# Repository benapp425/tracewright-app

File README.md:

<h1 align="center">Tracewright</h1>

<p align="center"><b>KiCad boards, designed with Claude.</b><br>
Describe a board or open one you have. Claude designs, places, routes and checks it with you,<br>
live in KiCad, then sends it to the fab.</p>

## Features

**Design with Claude**
- **A chat beside the board.** Claude reads the schematic and board, runs the checks and makes changes with its own design tools.
- **Start from a floorplan.** Drag the board's outline, mounting holes, connectors and main parts into place. Claude lays the board out from it.
- **Live in KiCad.** Placement and routing appear in KiCad's PCB Editor as Claude works.
- **You stay in control.** Claude keeps a visible plan, asks questions as cards and reads the notes you send while it works. Each turn shows what it changed and can be undone.
- **Edit it yourself.** Move, turn and lock parts, route tracks and pairs, tune lengths, draw pours and keep-outs on the board; change a part's value or footprint and rename nets on the schematic. ⌘Z undoes each step.
- **Flags as threads.** Flag a spot on the board or schematic with a request or a question, and draw on it: where a track should go, what to keep clear. Claude answers in the thread.
- **Needs your OK.** Nothing interrupts a run. Afterwards, a short list shows what Claude went ahead with that you may want to see (a swapped part, a moved connector, your own work changed), to keep or undo.
- **Notes that read like a person wrote them.** One short line on the sheet beside the part it explains; the reasoning and its sources in the design notes, shown when you hover the part.
- **Placement with reasons.** Pick a part to see why it is where it is. Keep parts near a pin, together, apart or at an edge; Claude places around it, in stages, and scores the result.
- **A routing plan.** Each net is routed by the router, routed first with its rules (pairs, clocks, switch nodes, heavy currents), or left for you (RF, current sense, high voltage), with its reason. Pick the router's preset and keep a net to chosen layers.
- **Up to 12 layers, and HDI.** Claude plans the stack-up and routes every signal layer. HDI (vias in pads, microvias, blind vias) stays off unless you turn it on.
- **Dense boards.** Before routing, each BGA is broken out: a via on every ball that needs one, each signal's escape out to the edge of the ball field layer by layer, and the parts under it moved off its via spots. Fine-pitch connectors get a via beside each pad, alternating sides. On a breakout board, the free GPIO move to the connector pins that lie the way they leave the chip. The router then negotiates: nets may cross at a rising price until none share copper, and it names the spots that stayed contested. The board says first whether it can be routed in its room and layers.
- **Pairs to their budget.** Click a pair to see its skew against what its interface allows; the route tunes pairs and length groups within their budgets.
- **Both sides from the start.** The setup's floorplan puts blocks and connectors on the top or the bottom.
- **Where tracks fit.** See the crowded parts of the board, hover any point to see what keeps a track out, and give an area its own rules (keep-out, no vias, finer tracks, more spacing).
- **Cost before you run.** See a request's likely cost and share of your plan's limit before you send it.
- **My parts.** Save parts you have checked, with their footprints, 3D models and notes, for every project.
- **Talk, attach, point.** Dictate a message, drop in pictures and data sheets, or type @ to point Claude at a part, net or sheet.
- **Run monitor.** A full-screen view of a run: the plan, the stages, the board as it grows, and how much of your Claude plan's limit is used.

**Check it**
- **62 design checks.** Schematic integrity (pinouts, packages, voltage domains), BOM, placement, routing quality, fab limits, assembly, signal integrity and power (regulators, heat, voltage drop, switchers, pours). Each says what it examined, and each is tested against a planted fault.
- **Simulate the board as laid out.** The voltage drop and current density in a supply's copper, the board's heat, where a fast net's return current runs (and the loop it opens round a gap), a net's impedance and edge at the far end with the series resistor that would tame it, crosstalk, a rail's impedance against its target, and circuit blocks from the schematic in ngspice.
- **Sign-off.** Before anything is ordered: the verdict, every requirement with its evidence (checks, calculations, simulations, regulator heat), the waivers you approved, and what only the built board can show.
- **Compare versions.** See what moved and which copper changed since any checkpoint.
- **Bring-up.** A checklist for the built board, with each reading checked against the plan, and a firmware starter: the pin map and a bring-up sketch from the schematic.

**Build it**
- **Order in one place.** JLCPCB turnkey or self-assembly, with a readiness list and a price estimate. Upload to PCBWay in one click.
- **Stock watch.** Warns when a part runs short of what an order needs, and finds in-stock stand-ins.
- **Save money.** Exact JLC Basic equivalents for Extended parts.
- **Parts lists.** For DigiKey, Mouser and LCSC.
- **Make.** The BOM's health, a test-point plan, a fab drawing and assembly drawings, a V-scored panel with rails and fiducials, the enclosure fit with an OpenSCAD box to start from, and your blocks: circuits that worked once, saved to use again.

## Download

1. Download **Tracewright-&lt;version&gt;-mac.zip** from the [latest release](../../releases/latest) and move **Tracewright.app** to Applications.
2. Open it with **right-click ▸ Open** the first time (the app is not notarized yet).
3. Tracewright installs its engine in `~/.tracewright-app`, then asks you to create an account.

### Requirements

- macOS 12 or later, on Apple silicon or Intel
- Python 3.10 or later ([python.org](https://www.python.org/downloads/macos/) or Homebrew)
- KiCad 9 or 10 ([kicad.org](https://www.kicad.org/download/macos/))
- [Claude Code](https://claude.com/claude-code), signed in, or an Anthropic API key
- Optional: Java 17+ and Freerouting 2.x for whole-board autorouting

## Install from source

```sh
git clone https://github.com/benapp425/tracewright-app.git && cd tracewright-app
sh install.sh
```

This installs Tracewright in `~/.tracewright-app`, adds the `tracewright` command, and builds
`~/Applications/Tracewright.app` (the Xcode command line tools are needed: `xcode-select --install`).
Run it again to update. `sh install.sh --uninstall` removes the app and keeps your projects and settings.
`tracewright doctor` reports what it found.

## Getting started

1. **Create your account.** The first account owns the app. Google sign-in can be set up in
   Settings ▸ Account. Forgot your password? Use **Forgot?** on the sign-in screen, or run
   `tracewright account reset EMAIL`.
2. **Finish setup.** Tracewright checks KiCad and Claude, then asks for a theme and a workflow.
3. **Start a project.** Describe a new board, import a KiCad project (or Altium, Eagle, PADS,
   CADSTAR, Fabmaster or P-CAD), open the demo, or get project ideas.
4. **Sign off and order.** Review the findings and waivers in Checks ▸ Sign-off and sign the design off. Parts ▸ Order then
   prepares the files and sends them to the fab.

To see Claude's edits live in KiCad, enable KiCad's API (**Preferences ▸ Plugins ▸ Enable KiCad API**),
restart KiCad and open the board in the PCB Editor.

## Project structure

```
my-board/
  tracewright.json      project settings: fab, sourcing, checks, stages
  BRIEF.md              the original description
  CLAUDE.md             instructions for Claude
  .claude/              skills for each stage, lessons, permissions
  hardware/<name>/      the KiCad project, with design-notes.json (the reasoning behind the schematic)
                        and placement-plan.json (why each part is where it is, and what to keep)
  design/               scripts Claude writes, and project-specific checks
  docs/                 requirements, architecture, decisions, parts, review, bring-up
  tools/tw/             the toolkit (./tw <command>), usable without the app
  build/                reports, plots and fab outputs (not in git)
```

Every project works without the app: `./tw check`, `./tw route`, `./tw escape`, `./tw space` and
`./tw outputs` run from the project folder, and Claude Code picks up the same instructions and skills there.

## Privacy

Tracewright runs on your Mac and keeps your projects there. When Claude works on a project, what it
reads (files, renders, check results) goes to Anthropic through your Claude Code sign-in or API key.
Part lookups query JLCPCB, LCSC and EasyEDA for the parts you look up, and once a day the stock watch asks
about the parts on a board you open (Settings ▸ Watch part stock turns it off). Dictation uses Apple's speech recognition, on the Mac when
it can; in a browser, the browser's own speech service. Board files are uploaded only
when you order or sync a project with GitHub. Accounts are stored in the app's data folder, with
passwords kept only as salted hashes. Once a day the app checks GitHub for a newer release
(Settings ▸ About turns this off).

## Server deployment

Tracewright can also run on a server as a web app, with accounts, uploads and GitHub import.
See [DEPLOY.md](DEPLOY.md).

## Development

```sh
python3 -m venv .venv && .venv/bin/pip install -e .
TW_ACCOUNTS=0 .venv/bin/python -m tracewright serve --port 8799   # no sign-in while developing
.venv/bin/python tests/run_tests.py                              # tests (some need KiCad)
.venv/bin/python tracewright/toolkit/tw/cli.py selftest          # every check catches its planted fault
sh macos/release.sh                                              # the downloadable app, in dist/
```

See [CHANGELOG.md](CHANGELOG.md) for release notes.

## License

MIT (see [LICENSE](LICENSE)). Tracewright works with, but does not include, KiCad (GPL-3.0+) and,
optionally, Freerouting (GPL-3.0). See [THIRD_PARTY.md](THIRD_PARTY.md).

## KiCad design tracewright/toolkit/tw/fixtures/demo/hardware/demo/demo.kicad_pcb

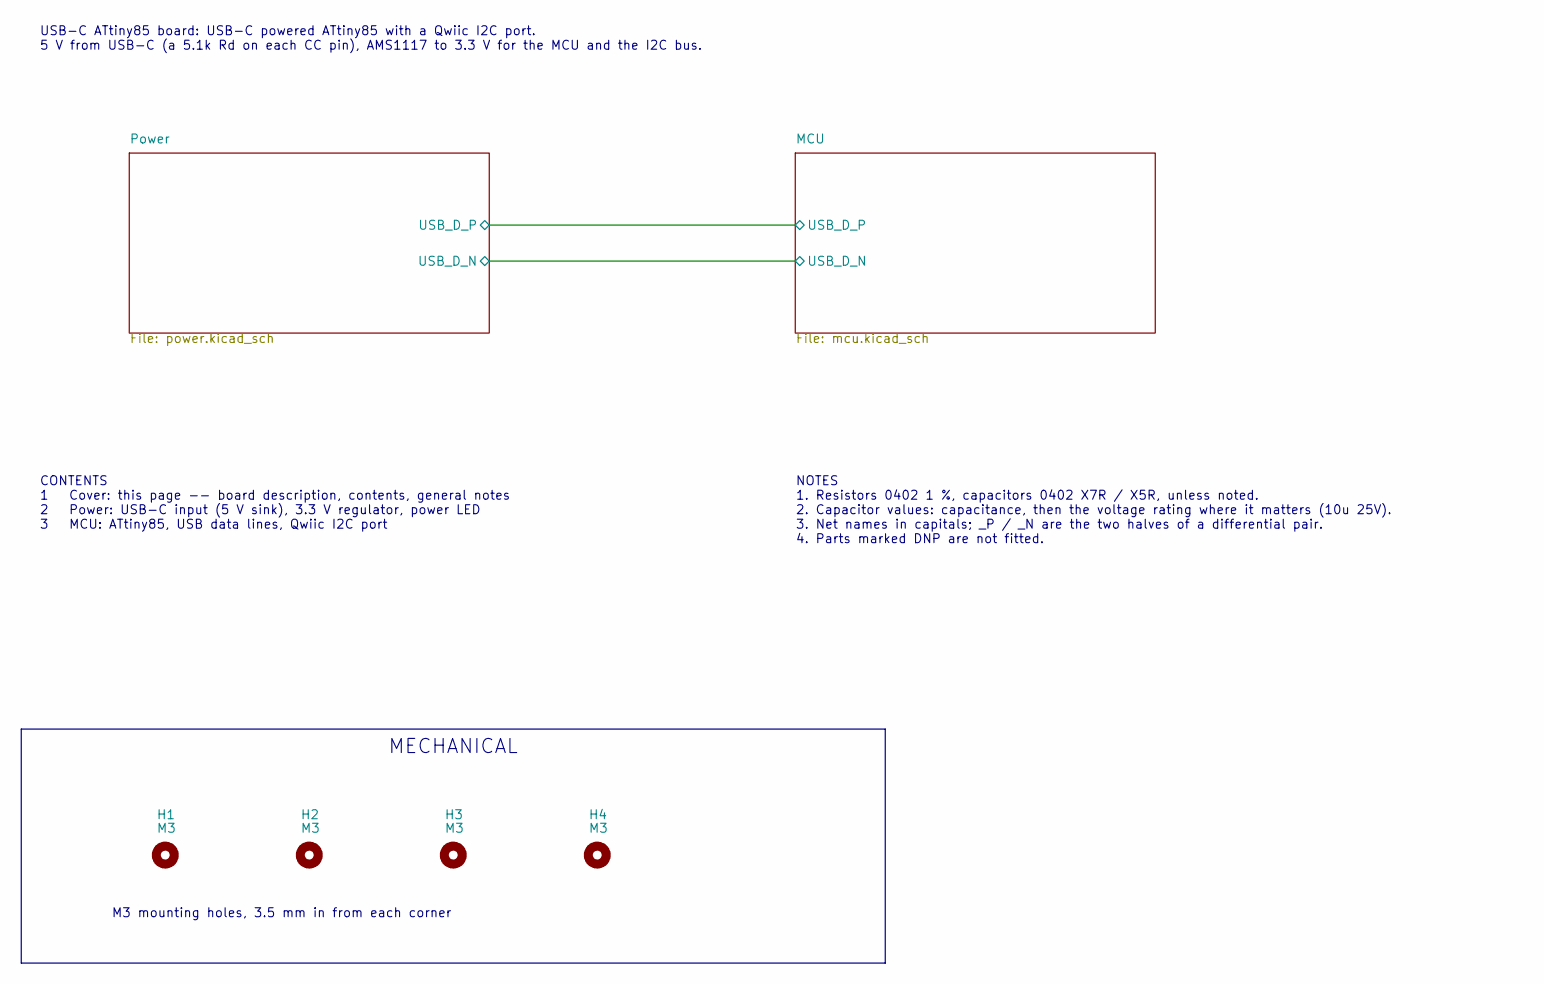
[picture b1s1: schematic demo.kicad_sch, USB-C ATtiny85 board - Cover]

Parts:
H1, H2, H3, H4: M3; MountingHole_3.2mm_M3

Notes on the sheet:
MECHANICAL
CONTENTS 1 Cover: this page -- board description, contents, general notes 2 Power: USB-C input (5 V sink), 3.3 V regulator, power LED 3 MCU: ATtiny85, USB data lines, Qwiic I2C port
NOTES 1. Resistors 0402 1 %, capacitors 0402 X7R / X5R, unless noted. 2. Capacitor values: capacitance, then the voltage rating where it matters (10u 25V). 3. Net names in capitals; _P / _N are the two halves of a differential pair. 4. Parts marked DNP are not fitted.
USB-C ATtiny85 board: USB-C powered ATtiny85 with a Qwiic I2C port. 5 V from USB-C (a 5.1k Rd on each CC pin), AMS1117 to 3.3 V for the MCU and the I2C bus.
M3 mounting holes, 3.5 mm in from each corner

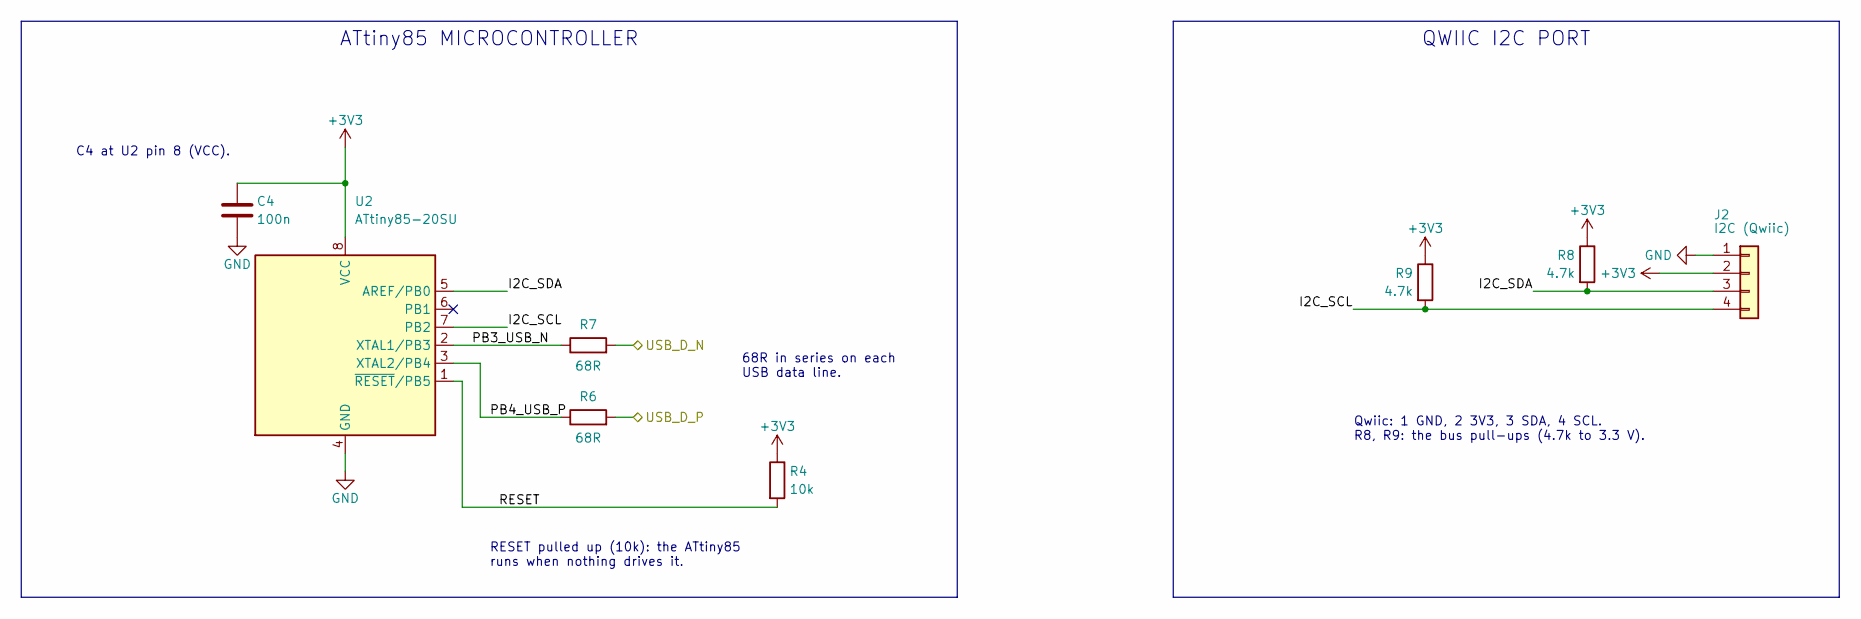
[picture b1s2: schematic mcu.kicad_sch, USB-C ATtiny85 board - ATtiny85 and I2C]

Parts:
C4: 100n; C_0402_1005Metric; MPN CL05B104KO5NNNC; LCSC C1525
J2: I2C (Qwiic); JST_SH_SM04B-SRSS-TB_1x04-1MP_P1.00mm_Horizontal; MPN SM04B-SRSS-TB(LF)(SN); LCSC C160404
R4: 10k; R_0402_1005Metric; MPN 0402WGF1002TCE; LCSC C25744
R6, R7: 68R; R_0402_1005Metric; MPN 0402WGF680JTCE; LCSC C25108
R8, R9: 4.7k; R_0402_1005Metric; MPN 0402WGF4701TCE; LCSC C25900
U2: ATtiny85-20SU; SOIC-8_5.3x5.3mm_P1.27mm; MPN ATTINY85-20SU; LCSC C31540447

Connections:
+3V3: C4.1, J2.2, R4.1, R8.1, R9.1, U2.8 (VCC); also elsewhere on the board
/MCU/I2C_SCL: J2.4, R9.2, U2.7 (PB2)
/MCU/I2C_SDA: J2.3, R8.2, U2.5 (AREF/PB0)
/MCU/PB3_USB_N: R7.1, U2.2 (XTAL1/PB3)
/MCU/PB4_USB_P: R6.1, U2.3 (XTAL2/PB4)
/MCU/RESET: R4.2, U2.1 (~RESET/PB5)
/MCU/USB_D_N: R7.2; also elsewhere on the board
/MCU/USB_D_P: R6.2; also elsewhere on the board
GND: C4.2, J2.1, U2.4 (GND); also elsewhere on the board

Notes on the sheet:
QWIIC I2C PORT
ATtiny85 MICROCONTROLLER
C4 at U2 pin 8 (VCC).
68R in series on each USB data line.
RESET pulled up (10k): the ATtiny85 runs when nothing drives it.
Qwiic: 1 GND, 2 3V3, 3 SDA, 4 SCL. R8, R9: the bus pull-ups (4.7k to 3.3 V).

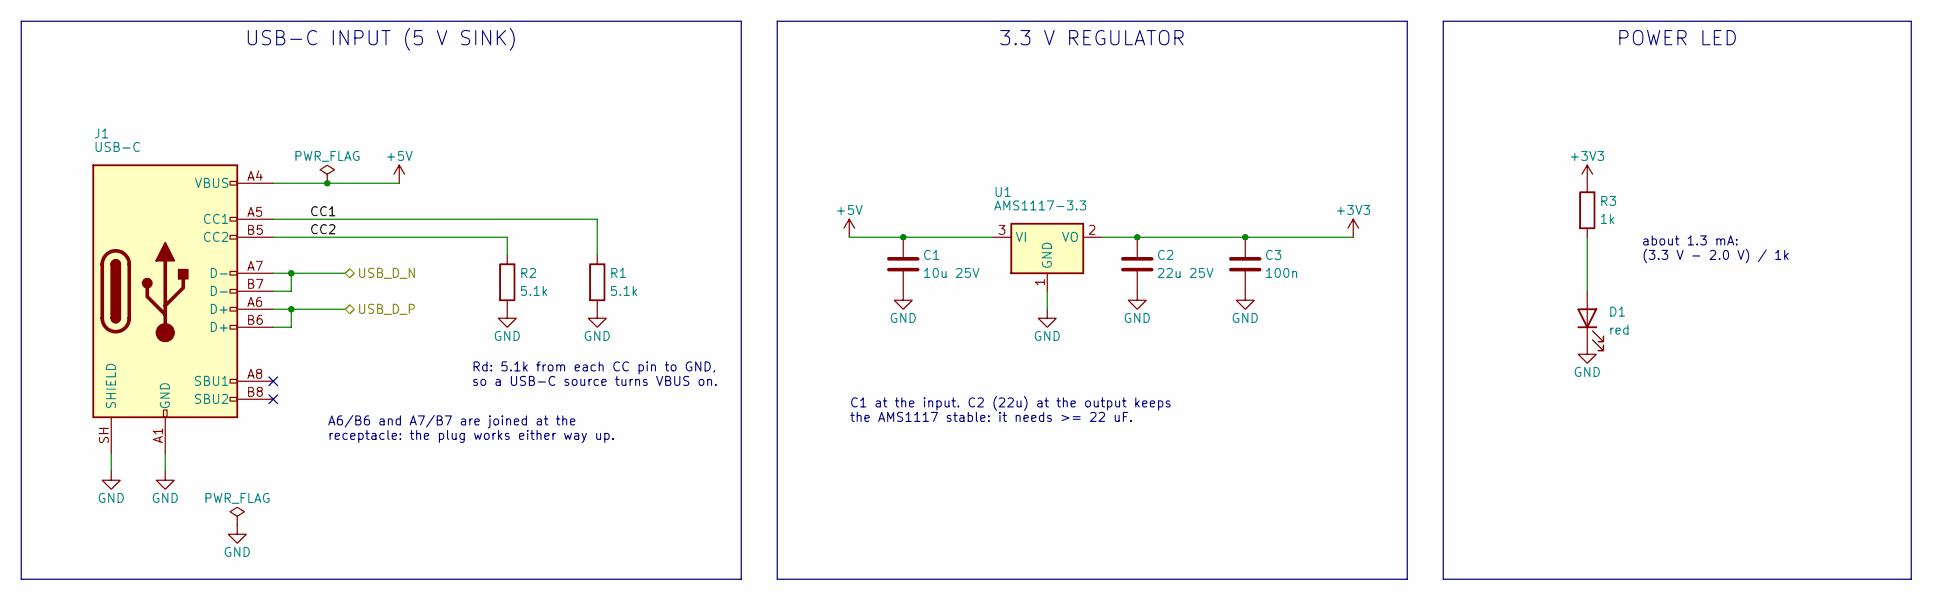
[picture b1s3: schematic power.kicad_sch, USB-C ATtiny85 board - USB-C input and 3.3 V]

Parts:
C1: 10u 25V; C_0805_2012Metric; MPN CL21A106KAYNNNE; LCSC C15850
C2: 22u 25V; C_1206_3216Metric; MPN CL31A226KAHNNNE; LCSC C12891
C3: 100n; C_0402_1005Metric; MPN CL05B104KO5NNNC; LCSC C1525
D1: red; LED_0603_1608Metric; MPN KT-0603R; LCSC C2286
J1: USB-C; USB_C_Receptacle_GCT_USB4105-xx-A_16P_TopMnt_Horizontal; MPN USB4105-GF-A; LCSC C3020560
R1, R2: 5.1k; R_0402_1005Metric; MPN 0402WGF5101TCE; LCSC C25905
R3: 1k; R_0402_1005Metric; MPN 0402WGF1001TCE; LCSC C11702
U1: AMS1117-3.3; SOT-223-3_TabPin2; MPN AMS1117-3.3; LCSC C6186

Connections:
+3V3: C2.1, C3.1, R3.1, U1.2 (VO); also elsewhere on the board
+5V: C1.1, J1.A4 (VBUS), J1.A9 (VBUS), J1.B4 (VBUS), J1.B9 (VBUS), U1.3 (VI)
/MCU/USB_D_N: J1.A7 (D-), J1.B7 (D-); also elsewhere on the board
/MCU/USB_D_P: J1.A6 (D+), J1.B6 (D+); also elsewhere on the board
/Power/CC1: J1.A5 (CC1), R1.1
/Power/CC2: J1.B5 (CC2), R2.1
GND: C1.2, C2.2, C3.2, D1.1 (K), J1.A1 (GND), J1.A12 (GND), J1.B1 (GND), J1.B12 (GND), J1.SH (SHIELD), R1.2, R2.2, U1.1 (GND); also elsewhere on the board
unnamed: D1.2 (A), R3.2

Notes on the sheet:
C1 at the input. C2 (22u) at the output keeps the AMS1117 stable: it needs >= 22 uF.
POWER LED
A6/B6 and A7/B7 are joined at the receptacle: the plug works either way up.
3.3 V REGULATOR
USB-C INPUT (5 V SINK)
Rd: 5.1k from each CC pin to GND, so a USB-C source turns VBUS on.
about 1.3 mA: (3.3 V - 2.0 V) / 1k

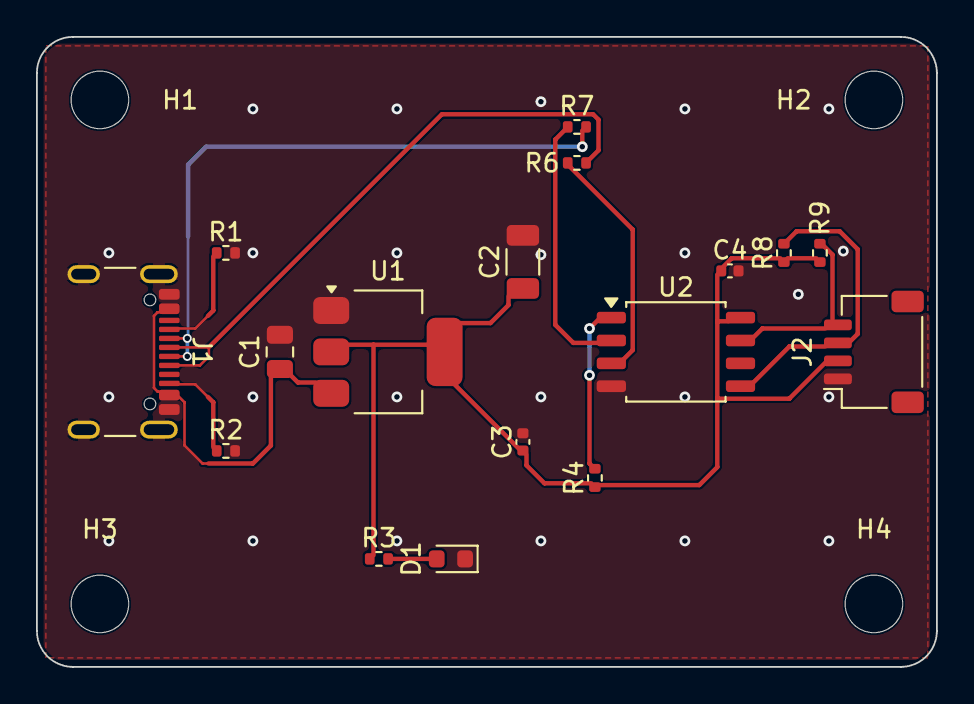
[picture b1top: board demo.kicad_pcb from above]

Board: 2 copper layers, 50.0 x 35.0 mm, 21 parts (0 on the bottom side), 13 nets.

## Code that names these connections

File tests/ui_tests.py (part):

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        for pd in f["pads"]:
            if pd["net"] and "F.Cu" in pd["l"]:
                pads.setdefault(pd["net"], []).append((f["ref"], pd))
    net = next(n for n in ("/MCU/PB3_USB_N", "/MCU/PB4_USB_P") if len(pads.get(n, [])) == 2)
    (ra, pa), (rb, pb) = pads[net]
    t.s.post(base + "/edit", {"ops": [{"op": "delete", "nets": [net]}], "label": "Clear " + net})
    await t.page.wait(f"{BV}.data && !{BV}.data.tracks.some((x) => x[6] === {json.dumps(net)})", 15)
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        check('(property "Value" "3.3k"' in open(os.path.join(hw, "mcu.kicad_sch")).read(), "the value was not written")
        await t.page.wait("document.querySelector('.inspector .in-title') && document.querySelector('.inspector .in-title').textContent.includes('3.3k')", 15)
        # a label on the sheet: rename its net
        await t.page.wait(f"{SV}.cur === {json.dumps(mcu)} && document.querySelector('.sch-label[data-text=\"I2C_SDA\"]')", 15)
        await t.page.js("document.querySelector('.sch-label[data-text=\"I2C_SDA\"]').dispatchEvent(new MouseEvent('click', { bubbles: true })); 1")
        await t.page.wait("document.querySelector('.rn-pop input')", 5)
        await t.shot("rename-net")
        await t.page.js("""(() => { const i = document.querySelector('.rn-pop input'); i.value = 'SDA';
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        # ⌘Z in the schematic view
        await t.page.js("document.activeElement && document.activeElement.blur && document.activeElement.blur(); document.dispatchEvent(new KeyboardEvent('keydown', { key: 'z', metaKey: true, bubbles: true })); 1")
        for _ in range(60):
            if open(os.path.join(hw, "mcu.kicad_sch")).read().count('(label "I2C_SDA"') == 2:
                break
            await asyncio.sleep(0.25)
        check(open(os.path.join(hw, "mcu.kicad_sch")).read().count('(label "I2C_SDA"') == 2, "⌘Z did not undo the rename")
        await t.page.wait(f"{SV}.history && {SV}.history.redo === 1", 10)
        await t.shot("schematic-edited")
    finally:
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        # return paths
        await t.page.js("document.querySelector('.sm-tabs button[data-sim=return]').click(); 1")
        await t.page.wait("document.querySelector('.sm-run')", 10)
        await t.page.js("(() => { const s = document.querySelector('.sm-ctl select'); s.value = [...s.options].find((o) => o.value === 'USB_D_P').value; s.dispatchEvent(new Event('change')); return 1; })()")
        await t.page.js(run)
        await t.page.wait("document.querySelector('.sm-lines') && document.querySelector('.sm-lines').innerText.includes(' over GND')", 60)
        await t.shot("simulate-return")
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        # signals: USB_D_P's edge
        await t.page.js("document.querySelector('.sm-tabs button[data-sim=signal]').click(); 1")
        await t.page.wait("document.querySelector('.sm-run')", 10)
        await t.page.js("(() => { const s = document.querySelector('.sm-ctl select'); s.value = 'USB_D_P'; s.dispatchEvent(new Event('change')); return 1; })()")
        await t.page.js(run)
        await t.page.wait("document.querySelector('.sm-svg svg') && document.querySelector('.sm-lines').innerText.includes('overshoot')", 90)
        check(await t.page.js("document.querySelectorAll('.sm-table tr').length") >= 2, "the impedance table")
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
